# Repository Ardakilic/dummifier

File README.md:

# Dummifier
Dummifier: A USB-3 to USB-2 with USB Type-C Port adapter where the the engineers fail to follow basic standards while designing the boards.

You just plug this dongle thingy between your device and your usb-c cable, and it'll start working as you expected.

# Why?

First of all, I needed this. Some devices that I own, such as [Planck keyboard](https://drop.com/buy/planck-mechanical-keyboard), [Anbernic RG351P](https://retrogamecorps.com/rg351/) utilized USB-C port, but they only worked when a cheap USB-C to USB-A cable was utilized, or through a USB Hub. They were not working at all with the USB-C cable I carry around, or getting wrong voltage and being burned. I burned my GP micro USB (I was using a USB-C to micro USB converter) battery charger because of this.

Additionally, I made some mods for Nintendo new 2DS XL for USB-C mod, and some cables were not working correctly.

Even newer Raspberry Pi Pico clones were having this issue.

The common workaround for this issue is using a USB Hub, or Cheap, non-standard, USB 2.0 Type A to USB-C 4 pin cables.

These cables are getting harder to find day by day.

I used to make some dummy cables for this purpose. Like [this](https://twitter.com/ardadev/status/1750195780932063600), [this](https://www.reddit.com/r/3DS/comments/whqvg9/made_a_usbc_converter_cable_that_works_with_usbc/) and [this](https://www.reddit.com/r/vitahacks/comments/uyd8oe/created_a_typec_adapter_for_my_vita_1000_that/). Functionality wise, they were all working, but damn they were ugly! Also, they had one thing in common. These populated 5.1K ohm resistors in CC1 and CC2 pins.

When I checked the [USB standards](https://www.usb.org/sites/default/files/USB%20Type-C%20Spec%20R2.0%20-%20August%202019.pdf) (page 38 and 76) , I realized these were necessary on female end so that the devices could talk to each other with USB 2.0 standards and get 5V instead of PD voltages.

After I burned my GP battery charger, I decided to tinker with Kicad and make my own adapter.

Some people even suggest using a [flex PCB mod that's soldered directly over the connector](https://github.com/ide/usb-c-to-c-power-mod) of these crappy designed devices, but this is not doable by everyone.

So, I decided I'd make a little converter like this. Anyone could use this. It's like a USB-C extension cable that you plug the male end to the bad device, and the female end to your favorite modern USB-C to USB-C cable.

I hope someone finds this helpful.

## Current status

* Tested, works nicely! Utilize only 5.1k resistors and 100nf cap (cap is optional). [Part from my Twitter flood, here](https://twitter.com/ardadev/status/1767934961703702860)
* Also, please be aware of the license of the project.

# Requirements

* Kicad 8
* If not set already, from PCB editor:
	* go to File / Board Setup
	* Set "Copper to Edge Clearance" to 0 (zero)

# TODOs

* Make VCC and GND lanes thicker.
* Export Gerber files directly for factory-ready printing.
* For better compatibility, [PCB design may need to be updated](https://www.reddit.com/r/UsbCHardware/comments/1ctkpf0/comment/l4fosnr/)

# Special Thanks

* [Ozkan Celik](https://github.com/ozkan). He helped me a lot during the design process and ideas.
* Ender Piyale, I gave him a lot of headache as well.
* Kazim Kaba, for case design.

# License
GNU GPL V3

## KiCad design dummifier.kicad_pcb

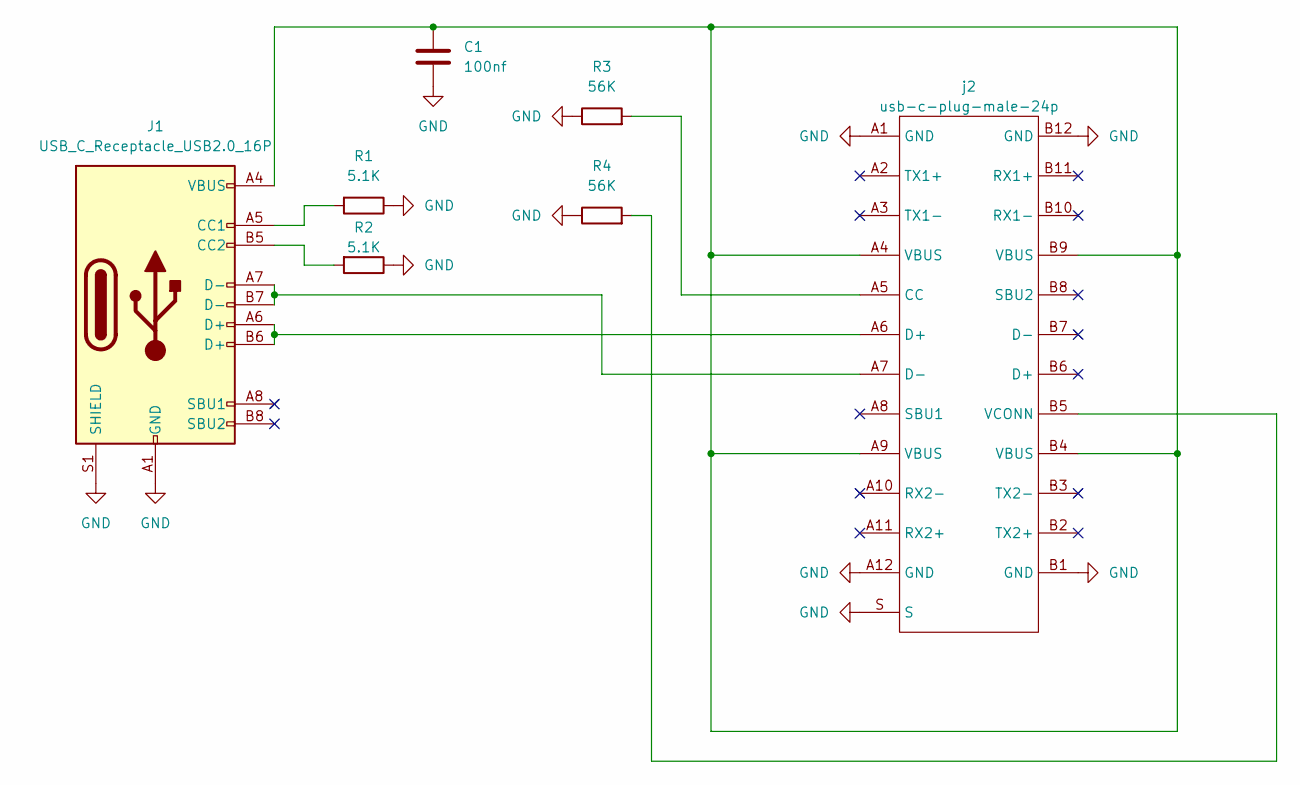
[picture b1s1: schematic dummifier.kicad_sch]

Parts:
C1: 100nf; C_0805_2012Metric_Pad1.18x1.45mm_HandSolder
J1: USB_C_Receptacle_USB2.0_16P; USB_C_Receptacle_HRO_TYPE-C-31-M-12
R1, R2: 5.1K; R_0805_2012Metric_Pad1.20x1.40mm_HandSolder
R3, R4: 56K; R_0805_2012Metric_Pad1.20x1.40mm_HandSolder
j2: usb-c-plug-male-24p; CONN_USBC-PLUG_24_PIN-2

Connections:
GND: C1.2, J1.A1 (GND), J1.A12 (GND), J1.B1 (GND), J1.B12 (GND), J1.S1 (SHIELD), R1.1, R2.1, R3.1, R4.1, j2.A1 (GND), j2.A12 (GND), j2.B1 (GND), j2.B12 (GND), j2.S
unnamed: C1.1, J1.A4 (VBUS), J1.A9 (VBUS), J1.B4 (VBUS), J1.B9 (VBUS), j2.A4 (VBUS), j2.A9 (VBUS), j2.B4 (VBUS), j2.B9 (VBUS)
unnamed: J1.A5 (CC1), R1.2
unnamed: J1.B5 (CC2), R2.2
unnamed: J1.A6 (D+), J1.B6 (D+), j2.A6 (D+)
unnamed: J1.A7 (D-), J1.B7 (D-), j2.A7 (D-)
unnamed: R3.2, j2.A5 (CC)
unnamed: R4.2, j2.B5 (VCONN)

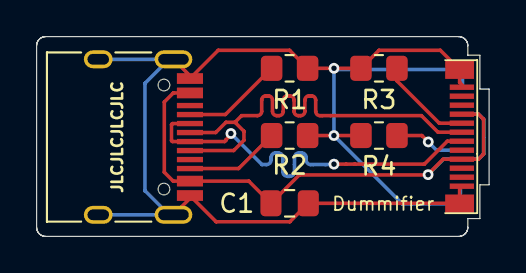
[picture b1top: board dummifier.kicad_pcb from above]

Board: 2 copper layers, 25.1 x 11.1 mm, 7 parts (0 on the bottom side), 8 nets.

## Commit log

2024-02-26 feature: upload the KiCad project file
2024-02-27 feature: Add Gerber files for v1.0
2024-05-16 Chore: Test status clarified on README
2024-10-27 feature: outer case design and outputs added
